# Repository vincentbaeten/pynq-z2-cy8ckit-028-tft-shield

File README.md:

# Shield for cy8ckit-028-tft on the PYNQ Z2

This is a simple shield for the [Infineon cy8ckit-028-tft](https://www.infineon.com/cms/en/product/evaluation-boards/cy8ckit-028-tft/). The purpose for this board is to use a couple extra pins on the raspberry pi header that are needed for the TFT-display.

## Pin mapping

| CY8CKIT-028-TFT | PYNQ-Z2 |
|-----------------|---------|
| ALS_OUT         | Y11     |
| IMU_INT1        | W11     |
| IMU_INT2        | V11     |
| PDM_CLK         | T5      |
| PDM_DATA        | U10     |
| SCL             | P16     |
| SDA             | P15     |
| CODEC_PDN       | Y12     |
| RX_SDI          | R16     |
| RX_WS           | T15     |
| RX_SCK          | V15     |
| TX_SDO          | V13     |
| TX_WS           | U13     |
| TX_SCK          | U12     |
| MCLK            | T14     |
| DISP_RST        | N17     |
| DISP_D/C        | P18     |
| DISP_WR         | R17     |
| DISP_RD         | T16     |
| DB8             | W9      |
| DB9             | Y9      |
| DB10            | A20     |
| DB11            | B19     |
| DB12            | B20     |
| DB13            | U17     |
| DB14            | V17     |
| DB15            | V18     |

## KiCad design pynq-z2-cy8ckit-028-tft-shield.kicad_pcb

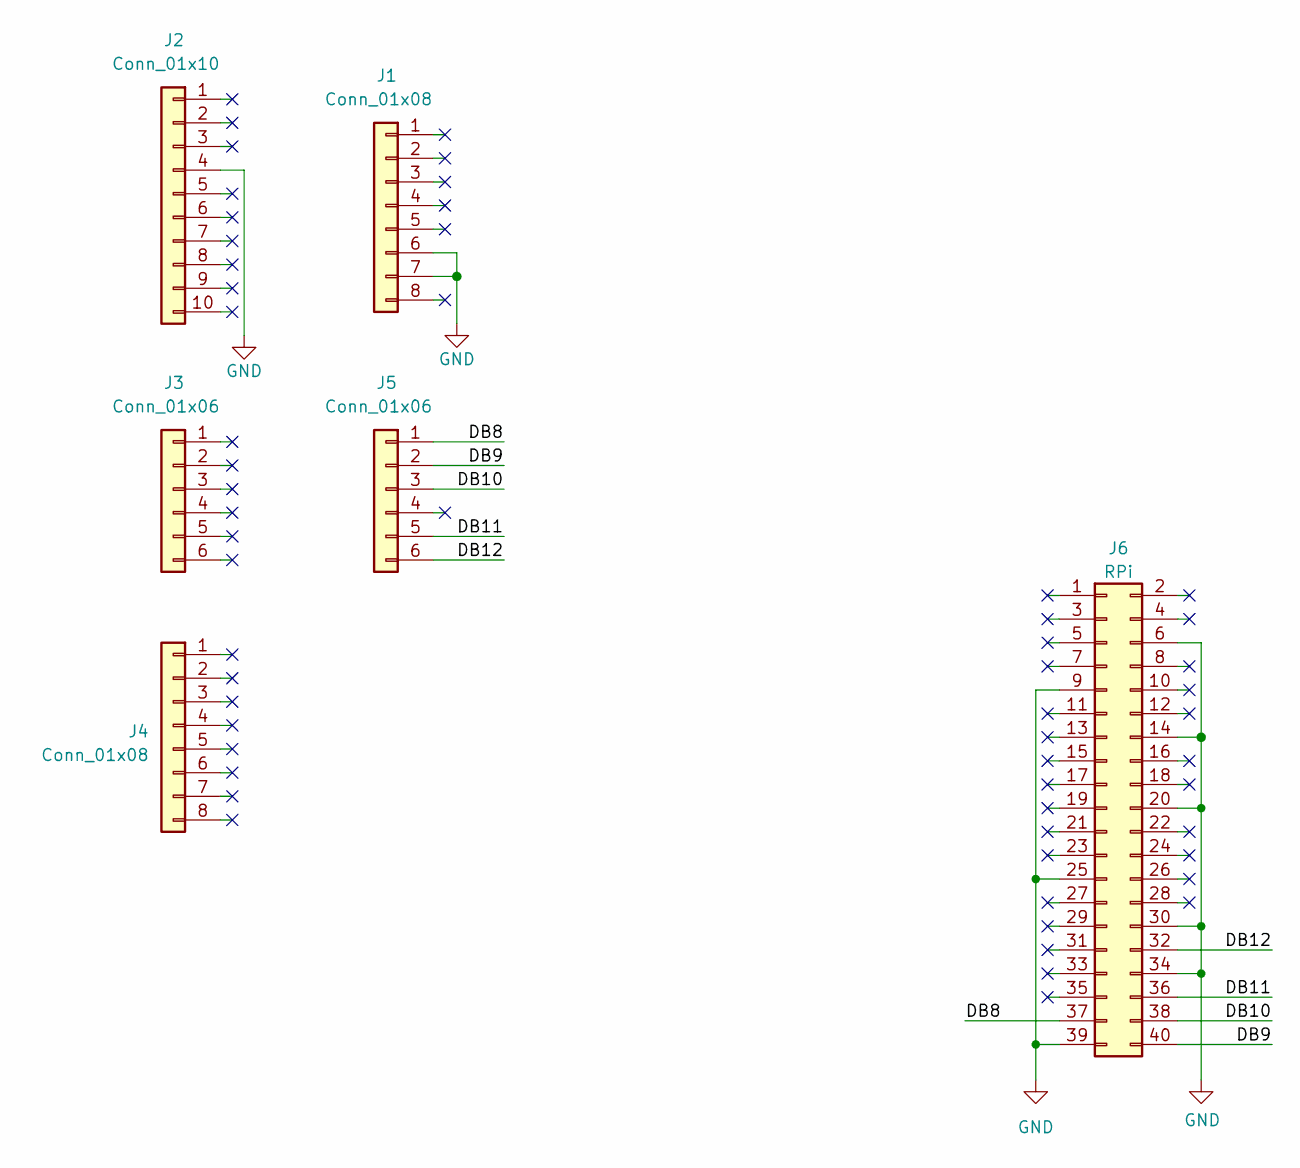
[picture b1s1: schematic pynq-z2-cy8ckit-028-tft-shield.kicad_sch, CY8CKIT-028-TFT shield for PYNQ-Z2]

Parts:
J1, J4: Conn_01x08; PinSocket_1x08_P2.54mm_Vertical
J2: Conn_01x10; PinSocket_1x10_P2.54mm_Vertical
J3, J5: Conn_01x06; PinSocket_1x06_P2.54mm_Vertical
J6: RPi; PinSocket_2x20_P2.54mm_Vertical

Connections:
/DB8: J5.1, J6.37
/DB9: J5.2, J6.40
/DB10: J5.3, J6.38
/DB11: J5.5, J6.36
/DB12: J5.6, J6.32
GND: J1.6, J1.7, J2.4, J6.6, J6.9, J6.14, J6.20, J6.25, J6.30, J6.34, J6.39

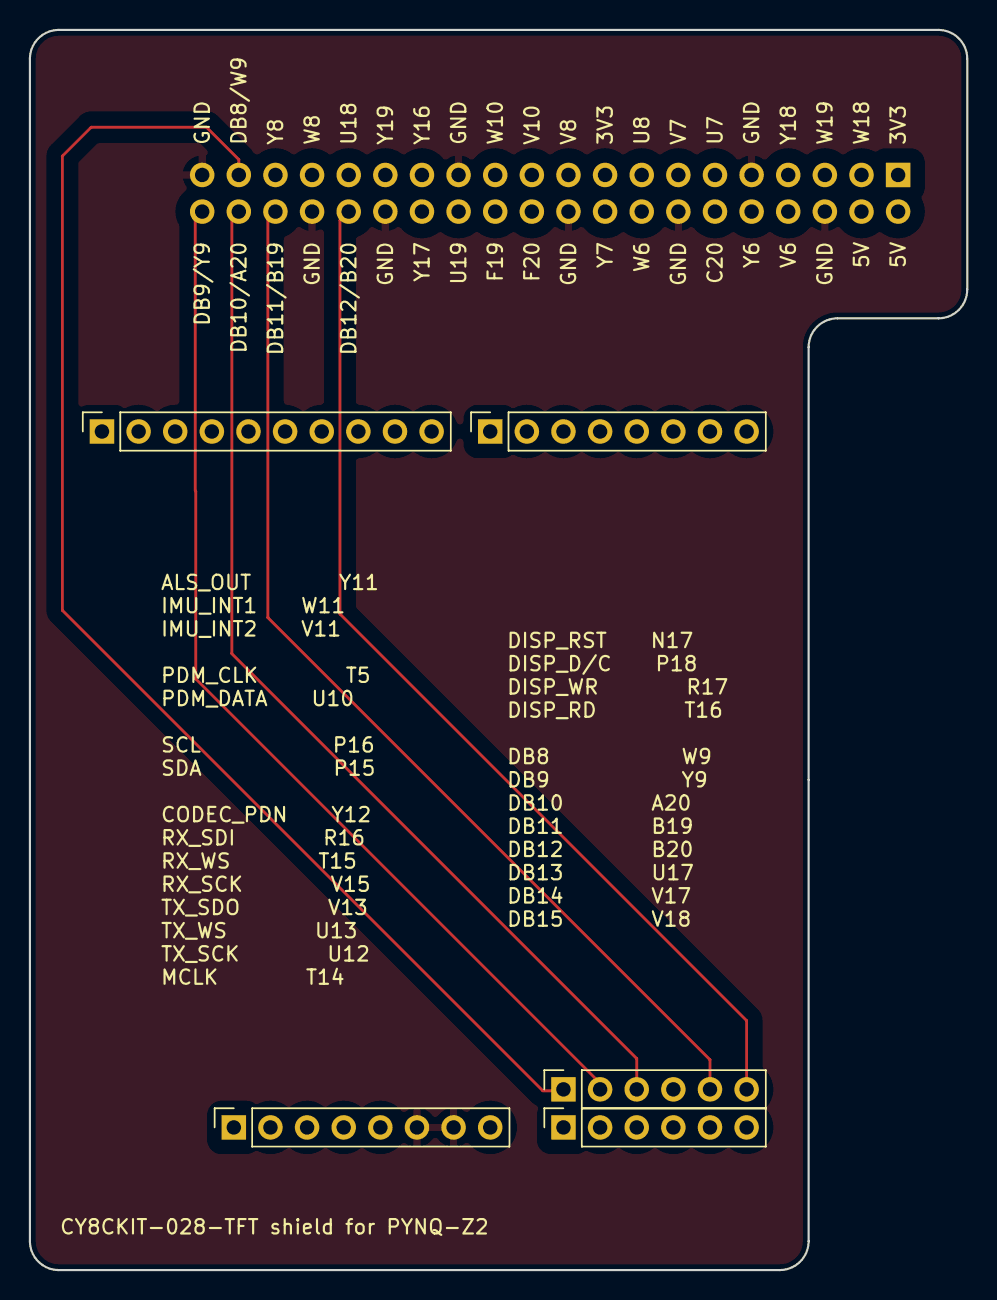
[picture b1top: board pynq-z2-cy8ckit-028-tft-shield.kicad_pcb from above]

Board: 2 copper layers, 65.0 x 86.0 mm, 6 parts (1 on the bottom side), 6 nets.

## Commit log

2023-04-06 Add .gitignore
2023-04-06 Add FreeCAD board dimensions
2023-04-06 Add schematic + pcb
2023-04-06 Add README.md
